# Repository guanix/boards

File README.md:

# KiCad schematic symbols and footprint libraries

I created these for my personal use, so they are not very organized.

These are no longer maintained.

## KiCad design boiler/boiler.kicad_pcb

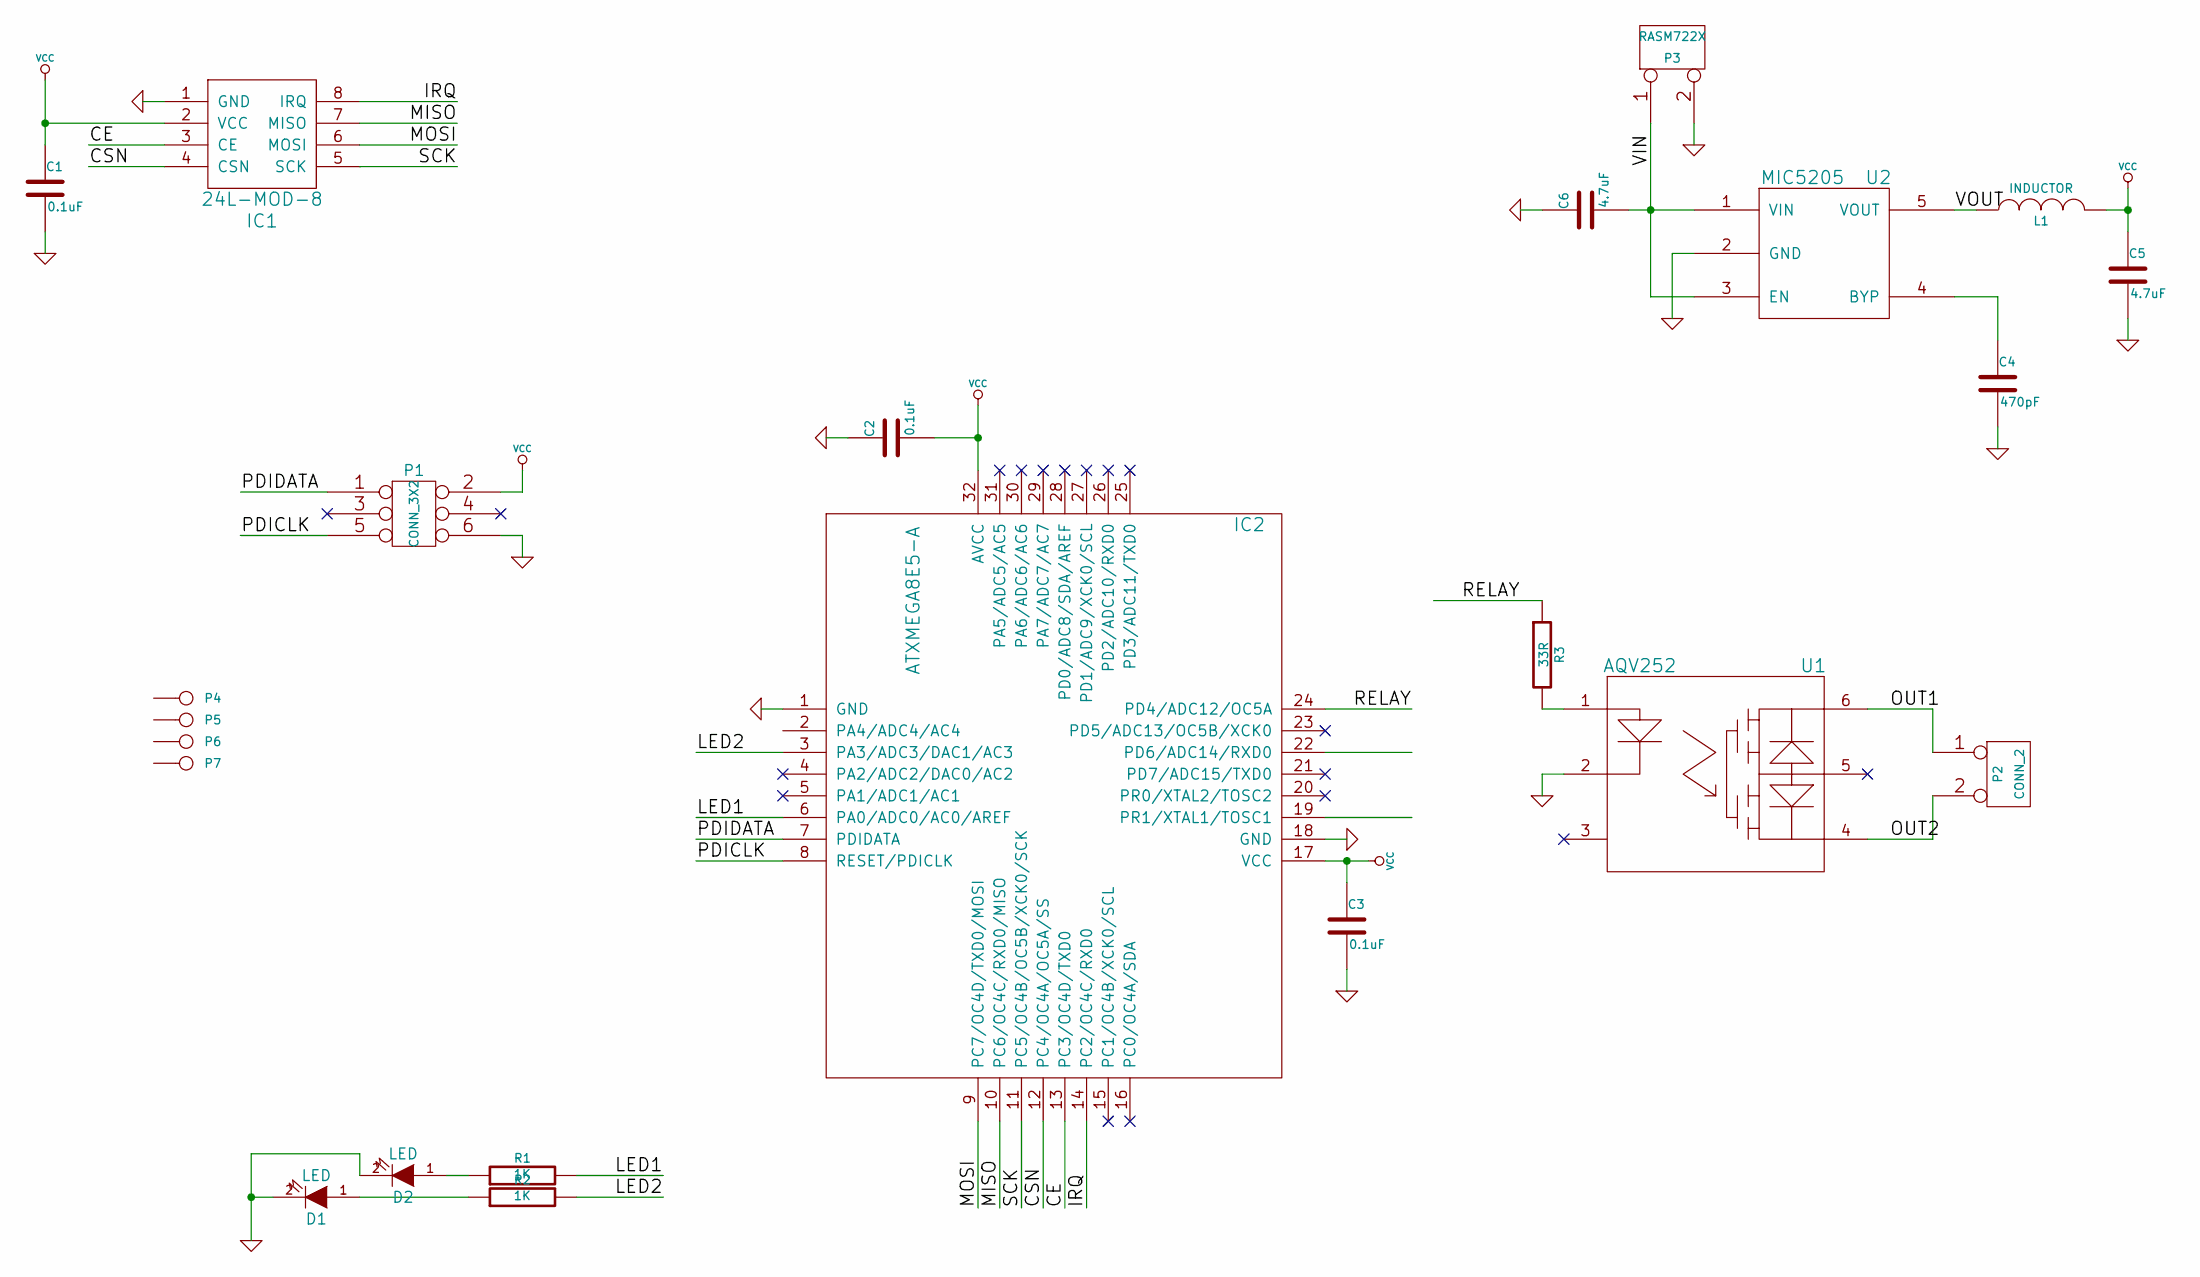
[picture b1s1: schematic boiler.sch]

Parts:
C1, C2, C3: 0.1uF
C4: 470pF
C5, C6: 4.7uF
D1, D2: LED
IC1: 24L-MOD-8
IC2: ATXMEGA8E5-A
L1: INDUCTOR
P1: CONN_3X2
P2: CONN_2
P3: RASM722X
P4, P5, P6, P7: CONN_1
R1, R2: 1K
R3: 33R
U1: AQV252
U2: MIC5205

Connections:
/CE: IC1.3 (CE), IC2.13 (PC3/OC4D/TXD0)
/CSN: IC1.4 (CSN), IC2.12 (PC4/OC4A/OC5A/SS)
/IRQ: IC1.8 (IRQ), IC2.14 (PC2/OC4C/RXD0)
/LED1: IC2.6 (PA0/ADC0/AC0/AREF), R1.2
/LED2: IC2.3 (PA3/ADC3/DAC1/AC3), R2.2
/MISO: IC1.7 (MISO), IC2.10 (PC6/OC4C/RXD0/MISO)
/MOSI: IC1.6 (MOSI), IC2.9 (PC7/OC4D/TXD0/MOSI)
/OUT1: P2.1, U1.6
/OUT2: P2.2 (PM), U1.4
/PDICLK: IC2.8 (RESET/PDICLK), P1.5
/PDIDATA: IC2.7 (PDIDATA), P1.1
/RELAY: IC2.24 (PD4/ADC12/OC5A), R3.1
/SCK: IC1.5 (SCK), IC2.11 (PC5/OC4B/OC5B/XCK0/SCK)
/VIN: C6.2, P3.1, U2.1 (VIN), U2.3 (EN)
/VOUT: L1.1, U2.5 (VOUT)
GND: C1.2, C2.1, C3.2, C4.2, C5.2, C6.1, D1.2 (K), D2.2 (K), IC1.1 (GND), IC2.1 (GND), IC2.18 (GND), P1.6, P3.2 (PM), U1.2, U2.2 (GND)
unnamed: C4.1, U2.4 (BYP)
unnamed: R3.2, U1.1
unnamed: D1.1 (A), R2.1
unnamed: D2.1 (A), R1.1
VCC: C1.1, C2.2, C3.1, C5.1, IC1.2 (VCC), IC2.17 (VCC), IC2.32 (AVCC), L1.2, P1.2

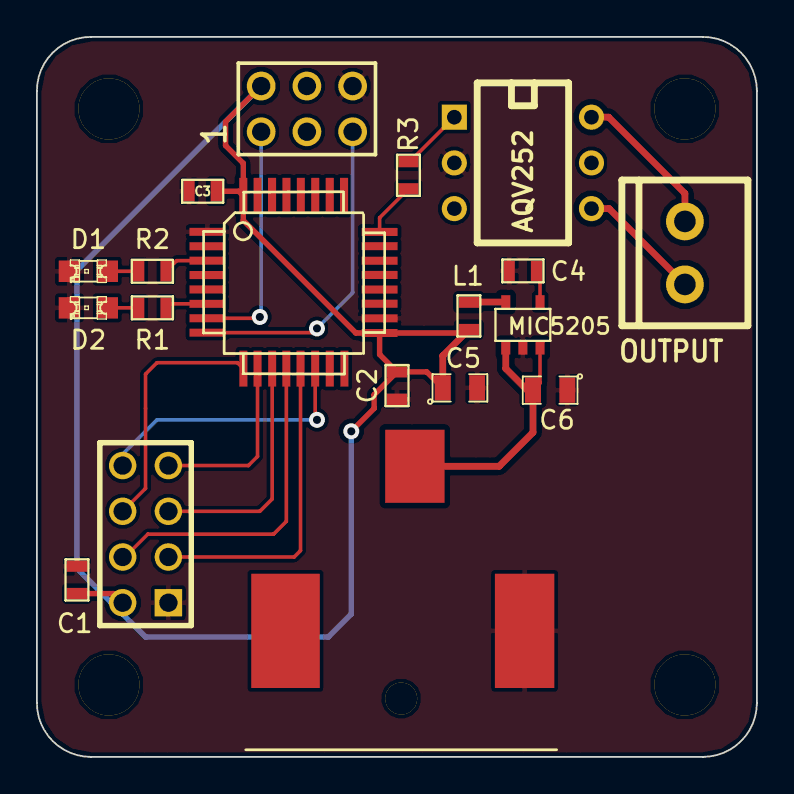
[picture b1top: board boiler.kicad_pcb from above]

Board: 2 copper layers, 40.0 x 40.0 mm, 23 parts (0 on the bottom side), 21 nets.

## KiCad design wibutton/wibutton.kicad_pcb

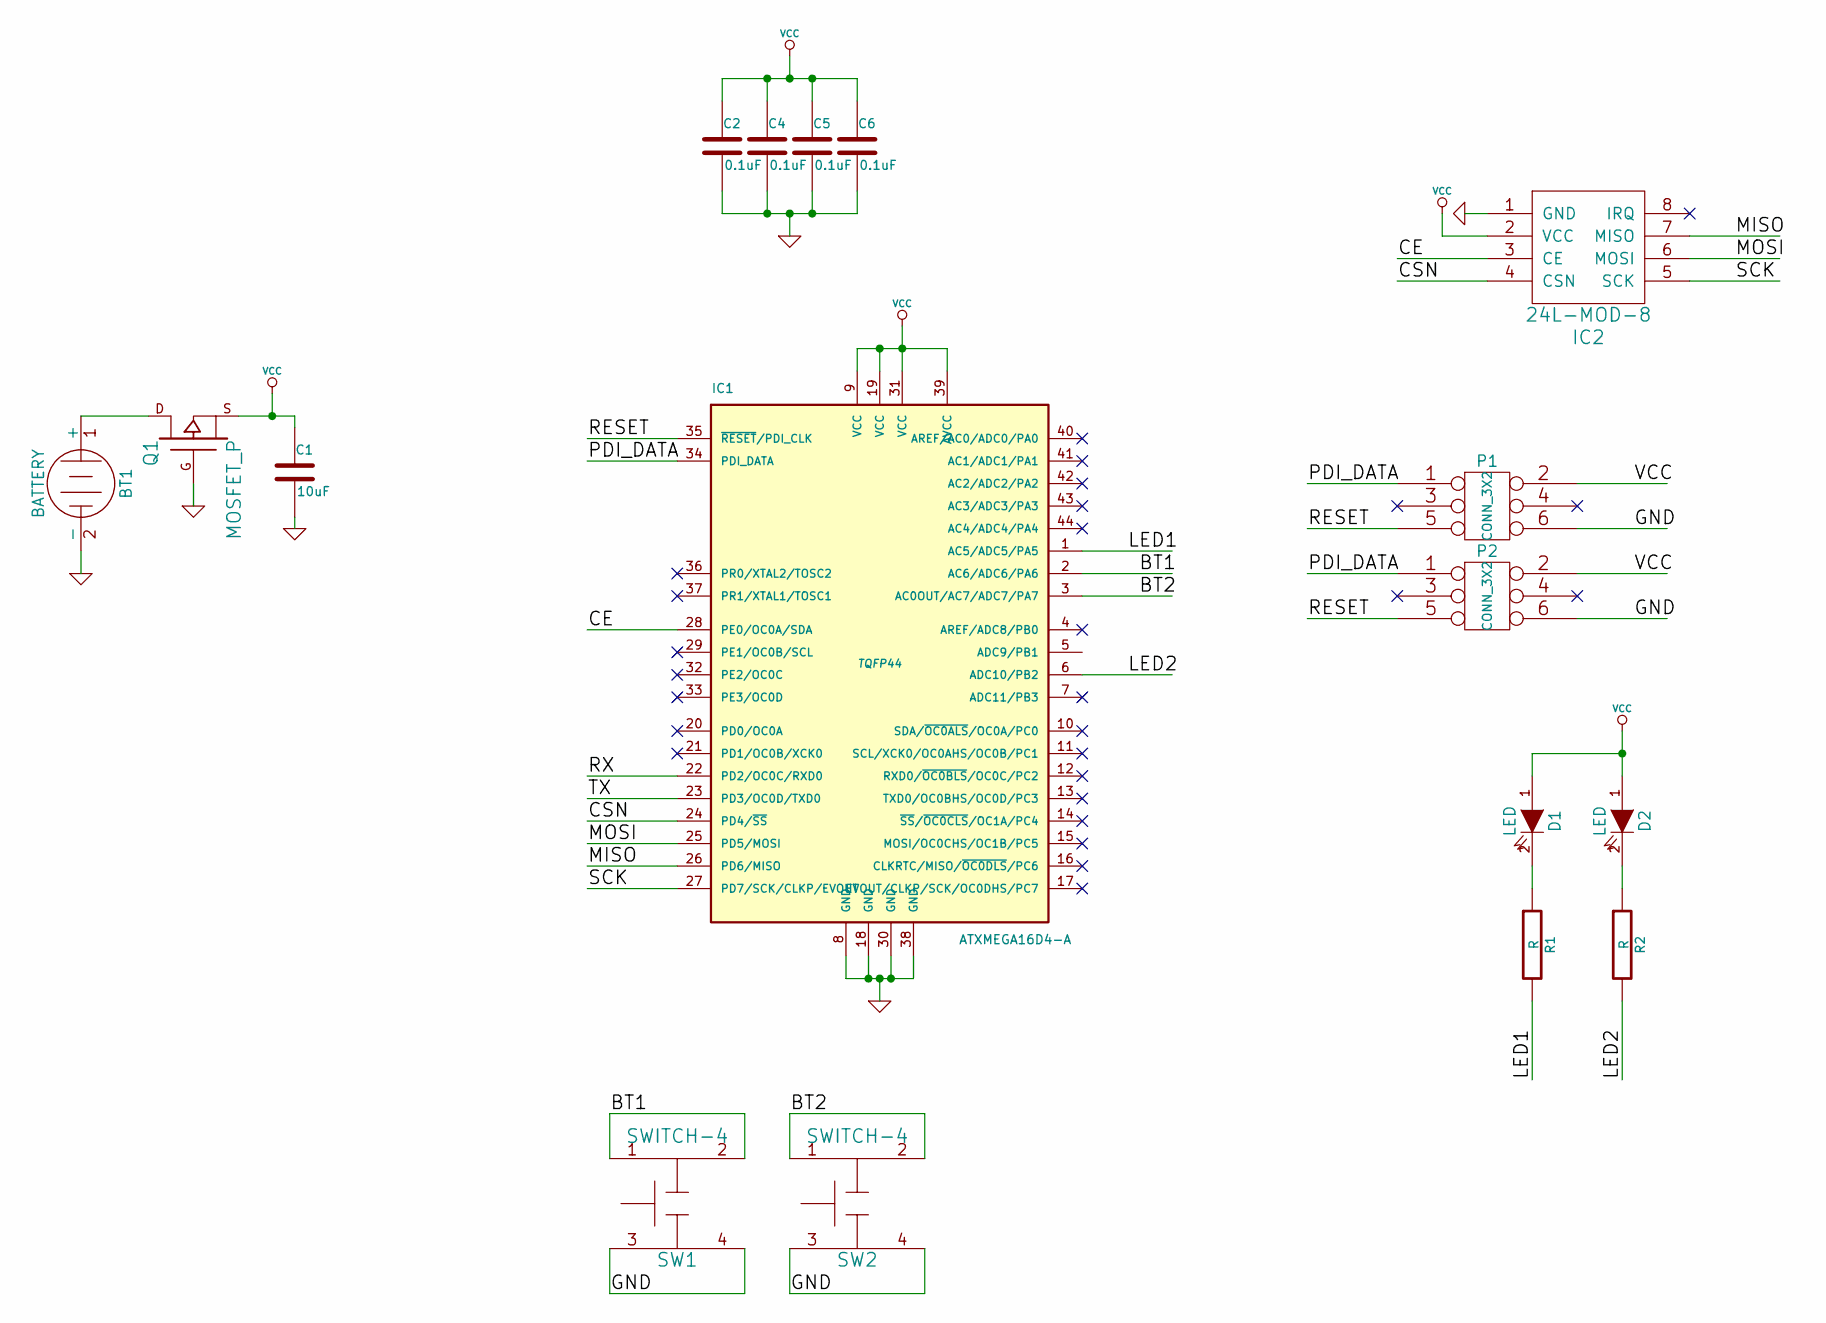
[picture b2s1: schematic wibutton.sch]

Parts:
BT1: BATTERY
C1: 10uF
C2, C4, C5, C6: 0.1uF
D1, D2: LED
IC1: ATXMEGA16D4-A; TQFP44
IC2: 24L-MOD-8
P1, P2: CONN_3X2
Q1: MOSFET_P
R1, R2: R
SW1, SW2: SWITCH-4

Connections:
/BT1: IC1.2 (AC6/ADC6/PA6), SW1.1, SW1.2
/BT2: IC1.3 (AC0OUT/AC7/ADC7/PA7), SW2.1, SW2.2
/CE: IC1.28 (PE0/OC0A/SDA), IC2.3 (CE)
/CSN: IC1.24 (PD4/~SS~), IC2.4 (CSN)
/LED1: IC1.1 (AC5/ADC5/PA5), R1.2
/LED2: IC1.6 (ADC10/PB2), R2.2
/MISO: IC1.26 (PD6/MISO), IC2.7 (MISO)
/MOSI: IC1.25 (PD5/MOSI), IC2.6 (MOSI)
/PDI_DATA: IC1.34 (PDI_DATA), P1.1, P2.1
/RESET: IC1.35 (~RESET~/PDI_CLK), P1.5, P2.5
/RX: IC1.22 (PD2/OC0C/RXD0)
/SCK: IC1.27 (PD7/SCK/CLKP/EVOUT), IC2.5 (SCK)
/TX: IC1.23 (PD3/OC0D/TXD0)
GND: BT1.2 (-), C1.2, C2.2, C4.2, C5.2, C6.2, IC1.8 (GND), IC1.18 (GND), IC1.30 (GND), IC1.38 (GND), IC2.1 (GND), P1.6, P2.6, Q1.G, SW1.3, SW1.4, SW2.3, SW2.4
unnamed: D1.2 (K), R1.1
unnamed: D2.2 (K), R2.1
unnamed: BT1.1 (+), Q1.D
VCC: C1.1, C2.1, C4.1, C5.1, C6.1, D1.1 (A), D2.1 (A), IC1.9 (VCC), IC1.19 (VCC), IC1.31 (VCC), IC1.39 (AVCC), IC2.2 (VCC), P1.2, P2.2, Q1.S

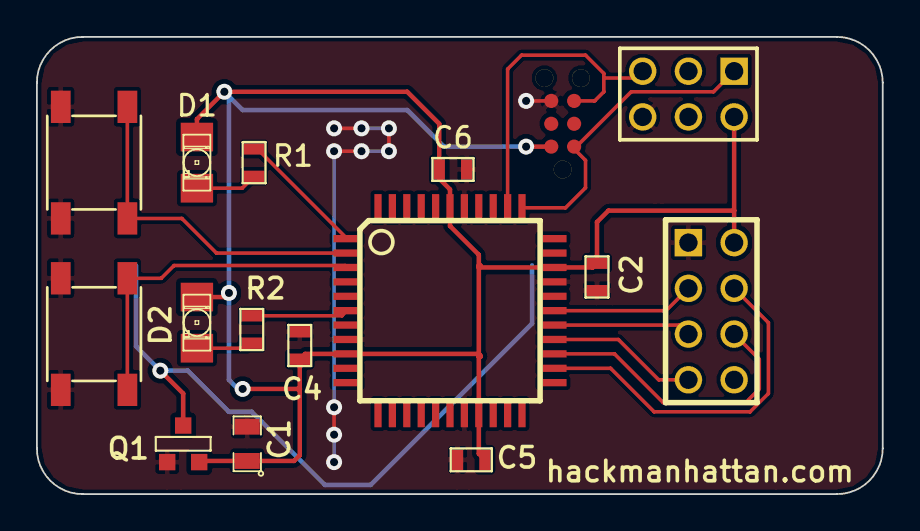
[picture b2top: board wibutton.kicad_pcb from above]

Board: 2 copper layers, 47.0 x 25.4 mm, 17 parts (1 on the bottom side), 16 nets.

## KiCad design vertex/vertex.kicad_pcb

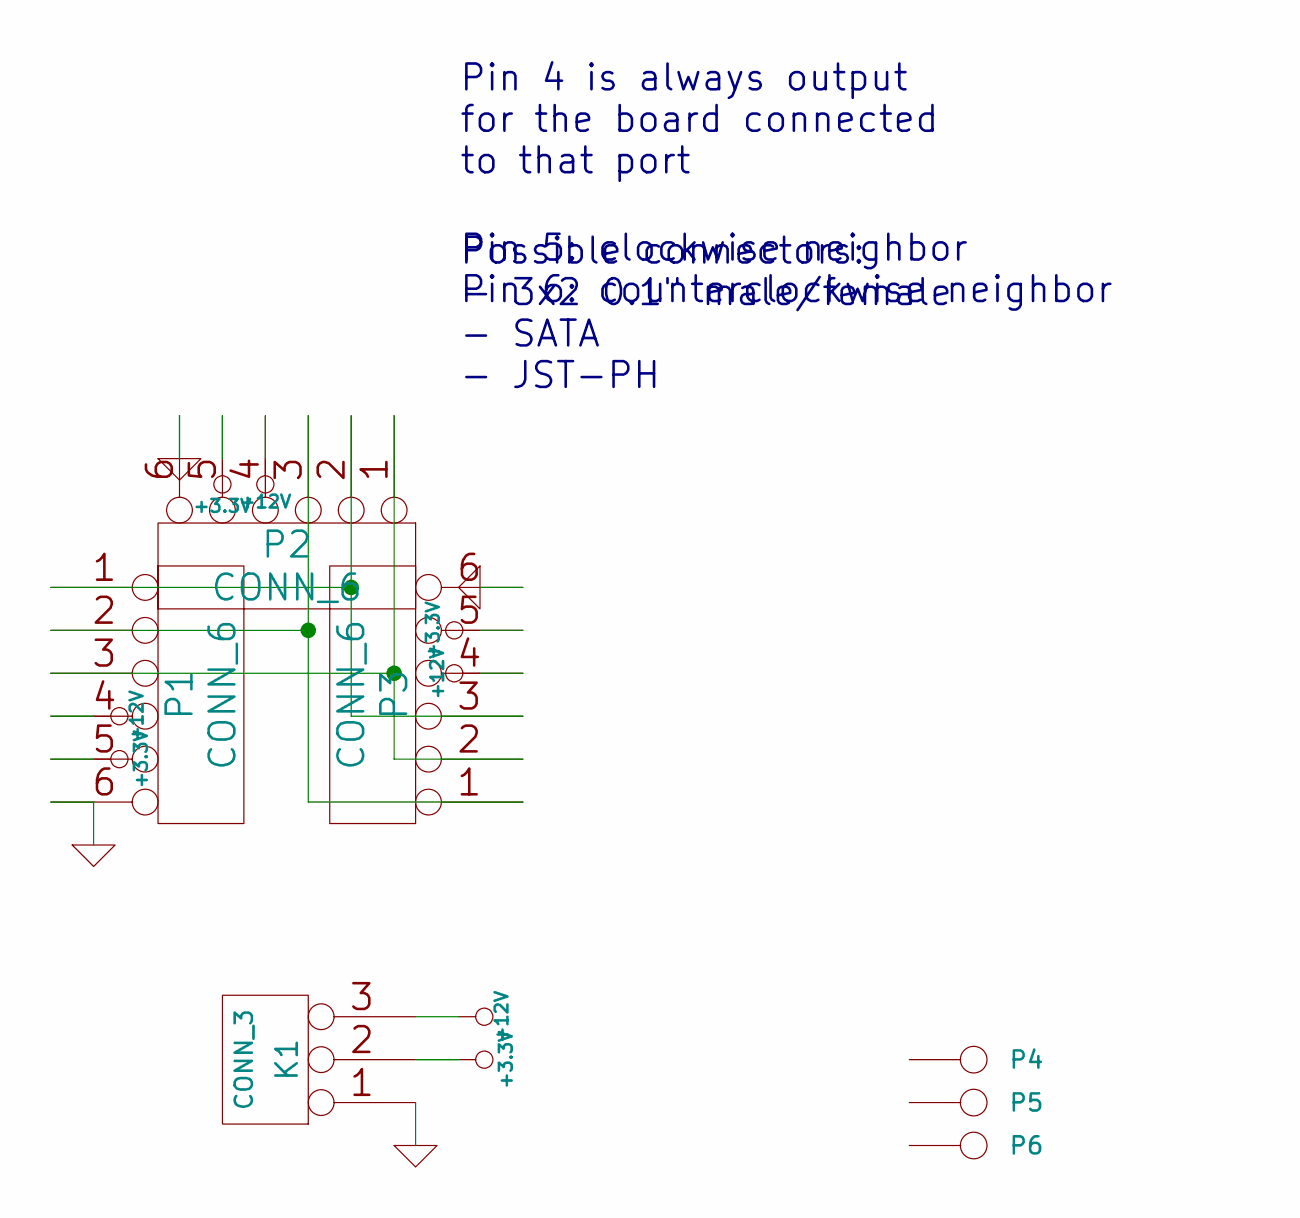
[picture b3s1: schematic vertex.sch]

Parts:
K1: CONN_3
P1, P2, P3: CONN_6
P4, P5, P6: CONN_1

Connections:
+3.3V: K1.2 (PM), P1.5, P2.5, P3.5
+12V: K1.3, P1.4, P2.4, P3.4
GND: K1.1, P1.6, P2.6, P3.6
unnamed: P1.2, P2.3, P3.1
unnamed: P1.3, P2.1, P3.2
unnamed: P1.1, P2.2, P3.3

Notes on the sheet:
Pin 4 is always output for the board connected to that port
Possible connectors: - 3x2 0.1" male/female - SATA - JST-PH
Pin 5: clockwise neighbor Pin 6: counterclockwise neighbor

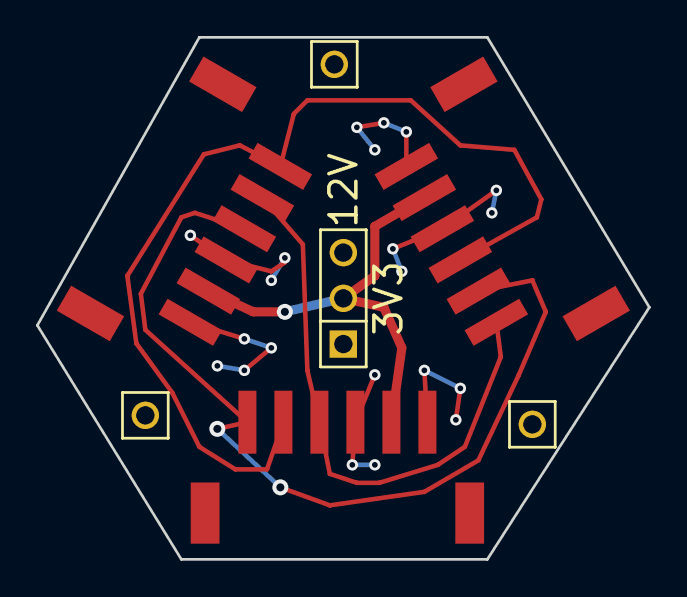
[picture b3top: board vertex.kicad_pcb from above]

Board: 2 copper layers, 34.0 x 29.0 mm, 7 parts (0 on the bottom side), 6 nets.

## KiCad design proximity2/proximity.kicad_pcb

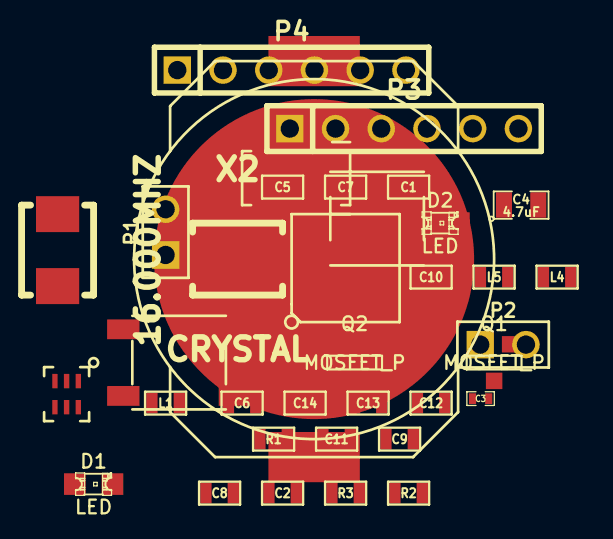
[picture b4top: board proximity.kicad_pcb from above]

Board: 2 copper layers, 36 parts (0 on the bottom side), 34 nets, no tracks yet.

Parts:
B1: BALUN-JOHANSON
BT1: BATTERY; BAT-BK912
C1, C2, C8, C11: 0.1uF; SM0603
C3: 2.2nF; SM0402
C4: 4.7uF; SM0805
C5, C6, C13, C14: 12pF; SM0603
C7: 4.7uF; SM0603
C9: 1nF; SM0603
C10: 47nF; SM0603
C12: 1uF; SM0603
D1, D2: LED; LED-0805
IC1: NRF51822; QFN48+1-0.4MM-SHORTPADS
L1: INDUCTOR; SM0603
L4: 10uH; SM0603
L5: 15nH; SM0603
P1, P2: CONN_2; PIN_ARRAY_2X1
P3: AIN_0_3; PIN_ARRAY-6X1
P4: AIN_4_7; PIN_ARRAY-6X1
Q1, Q2: MOSFET_P; SOT23GDS
R1: 12K; SM0603
R2, R3: 100R; SM0603
SW1, SW2: SWITCH-4; SWITCH-ALPS
U1: ANTENNA-NC; ANTENNA-JOHANSON-2.45GHZ
X1: 16.000MHZ; CRYSTAL-NX5032GA
X2: CRYSTAL; CRYSTAL-NX5032GA

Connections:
/AIN2: IC1.5, P3.5
/AIN3: IC1.6, P3.6
/AIN4: IC1.7, P4.3
/AIN5: IC1.8, P4.4
/AIN6: IC1.9, P4.5
/AIN7: IC1.10, P4.6
/ANT1: B1.4, IC1.31
/ANT2: B1.3, IC1.32
/LED1: IC1.15, R2.2
/LED2: IC1.16, R3.2
/P7: IC1.11, P3.3
/P8: IC1.14, P3.4
/SW1: IC1.48, SW1.3, SW1.4
/SW2: IC1.47, SW2.3, SW2.4
/SWCLK: IC1.24, P1.2, R1.1
/SWDIO: IC1.23, P1.1
/VDD_PA: B1.5, C3.1, IC1.30
AVDD: C9.1, C12.1, IC1.35, IC1.36, L5.1
GND: B1.2, BT1.2, C2.1, C3.2, C4.2, C5.1, C6.1, C7.2, C8.2, C9.2, C10.2, C11.2, C12.2, C13.1, C14.1, IC1.13, IC1.33, IC1.34, IC1.49, P2.2, P3.1, P4.1, Q1.G, Q2.G, R1.2, SW1.1, SW1.2, SW2.1, SW2.2
unnamed: C10.1, IC1.29
unnamed: D2.2, R3.1
unnamed: D1.2, R2.1
unnamed: B1.1, U1.1
unnamed: L4.1, L5.2
unnamed: C5.2, IC1.38, X1.2
unnamed: C6.2, IC1.37, X1.1
unnamed: C8.1, IC1.39
unnamed: IC1.2, L4.2
unnamed: C14.2, IC1.45, X2.2
unnamed: C13.2, IC1.46, X2.1
unnamed: P2.1, Q1.D
unnamed: L1.1, Q1.S, Q2.S
unnamed: BT1.1, Q2.D
VCC: C1.2, C2.2, C4.1, C7.1, C11.1, D1.1, D2.1, IC1.1, IC1.12, L1.2, P3.2, P4.2

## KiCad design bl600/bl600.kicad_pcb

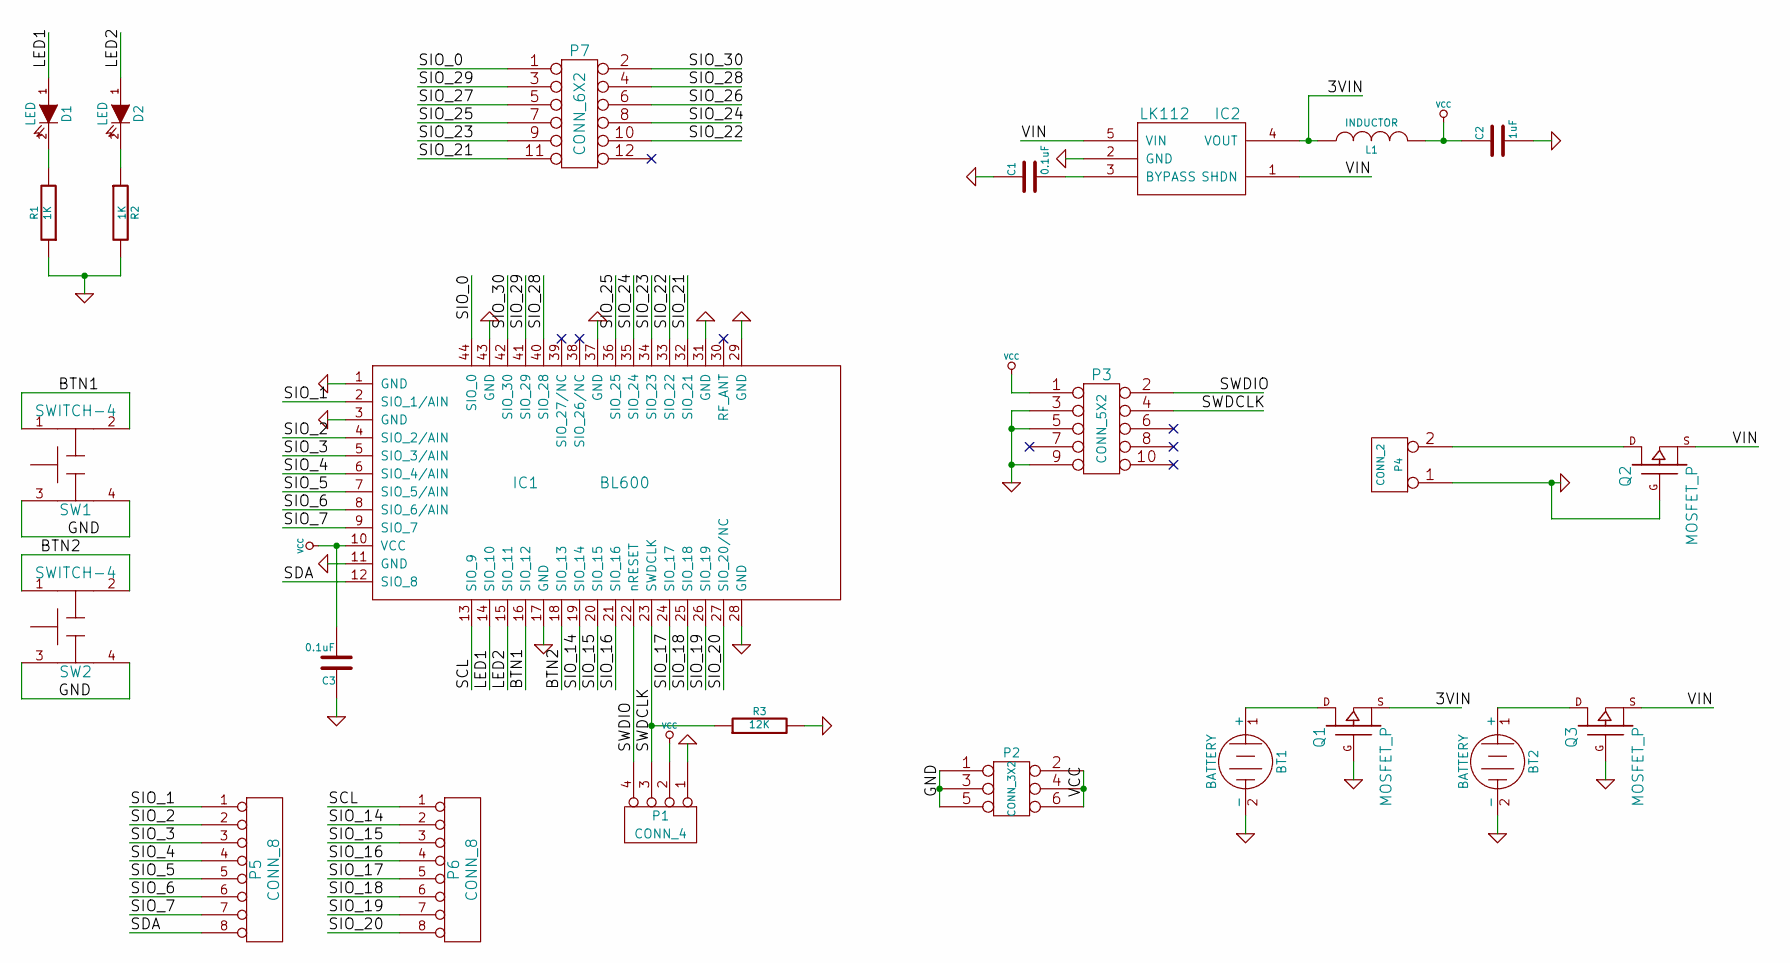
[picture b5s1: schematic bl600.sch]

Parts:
BT1, BT2: BATTERY
C1, C3: 0.1uF
C2: 1uF
D1, D2: LED
IC1: BL600
IC2: LK112
L1: INDUCTOR
P1: CONN_4
P2: CONN_3X2
P3: CONN_5X2
P4: CONN_2
P5, P6: CONN_8
P7: CONN_6X2
Q1, Q2, Q3: MOSFET_P
R1, R2: 1K
R3: 12K
SW1, SW2: SWITCH-4

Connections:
/3VIN: IC2.4 (VOUT), L1.1, Q1.S
/BTN1: IC1.16 (SIO_12), SW1.1, SW1.2
/BTN2: IC1.18 (SIO_13), SW2.1, SW2.2
/LED1: D1.1 (A), IC1.14 (SIO_10)
/LED2: D2.1 (A), IC1.15 (SIO_11)
/SCL: IC1.13 (SIO_9), P6.1
/SDA: IC1.12 (SIO_8), P5.8
/SIO_0: IC1.44 (SIO_0), P7.1
/SIO_1: IC1.2 (SIO_1/AIN), P5.1
/SIO_2: IC1.4 (SIO_2/AIN), P5.2
/SIO_3: IC1.5 (SIO_3/AIN), P5.3
/SIO_4: IC1.6 (SIO_4/AIN), P5.4
/SIO_5: IC1.7 (SIO_5/AIN), P5.5
/SIO_6: IC1.8 (SIO_6/AIN), P5.6
/SIO_7: IC1.9 (SIO_7), P5.7
/SIO_14: IC1.19 (SIO_14), P6.2
/SIO_15: IC1.20 (SIO_15), P6.3
/SIO_16: IC1.21 (SIO_16), P6.4
/SIO_17: IC1.24 (SIO_17), P6.5
/SIO_18: IC1.25 (SIO_18), P6.6
/SIO_19: IC1.26 (SIO_19), P6.7
/SIO_20: IC1.27 (SIO_20/NC), P6.8
/SIO_21: IC1.32 (SIO_21), P7.11
/SIO_22: IC1.33 (SIO_22), P7.10
/SIO_23: IC1.34 (SIO_23), P7.9
/SIO_24: IC1.35 (SIO_24), P7.8
/SIO_25: IC1.36 (SIO_25), P7.7
/SIO_26: P7.6
/SIO_27: P7.5
/SIO_28: IC1.40 (SIO_28), P7.4
/SIO_29: IC1.41 (SIO_29), P7.3
/SIO_30: IC1.42 (SIO_30), P7.2
/SWDCLK: IC1.23 (SWDCLK), P1.3, P3.4, R3.1
/SWDIO: IC1.22 (nRESET), P1.4, P3.2
/VIN: IC2.1 (SHDN), IC2.5 (VIN), Q2.S, Q3.S
GND: BT1.2 (-), BT2.2 (-), C1.1, C2.2, C3.1, IC1.1 (GND), IC1.3 (GND), IC1.11 (GND), IC1.17 (GND), IC1.28 (GND), IC1.29 (GND), IC1.31 (GND), IC1.37 (GND), IC1.43 (GND), IC2.2 (GND), P1.1, P2.1, P2.3, P2.5, P3.3, P3.5, P3.9, P4.1, Q1.G, Q2.G, Q3.G, R1.1, R2.2, R3.2, SW1.3, SW1.4, SW2.3, SW2.4
unnamed: D2.2 (K), R2.1
unnamed: D1.2 (K), R1.2
unnamed: BT1.1 (+), Q1.D
unnamed: P4.2 (PM), Q2.D
unnamed: BT2.1 (+), Q3.D
unnamed: C1.2, IC2.3 (BYPASS)
VCC: C2.1, C3.2, IC1.10 (VCC), L1.2, P1.2, P2.2, P2.4, P2.6, P3.1

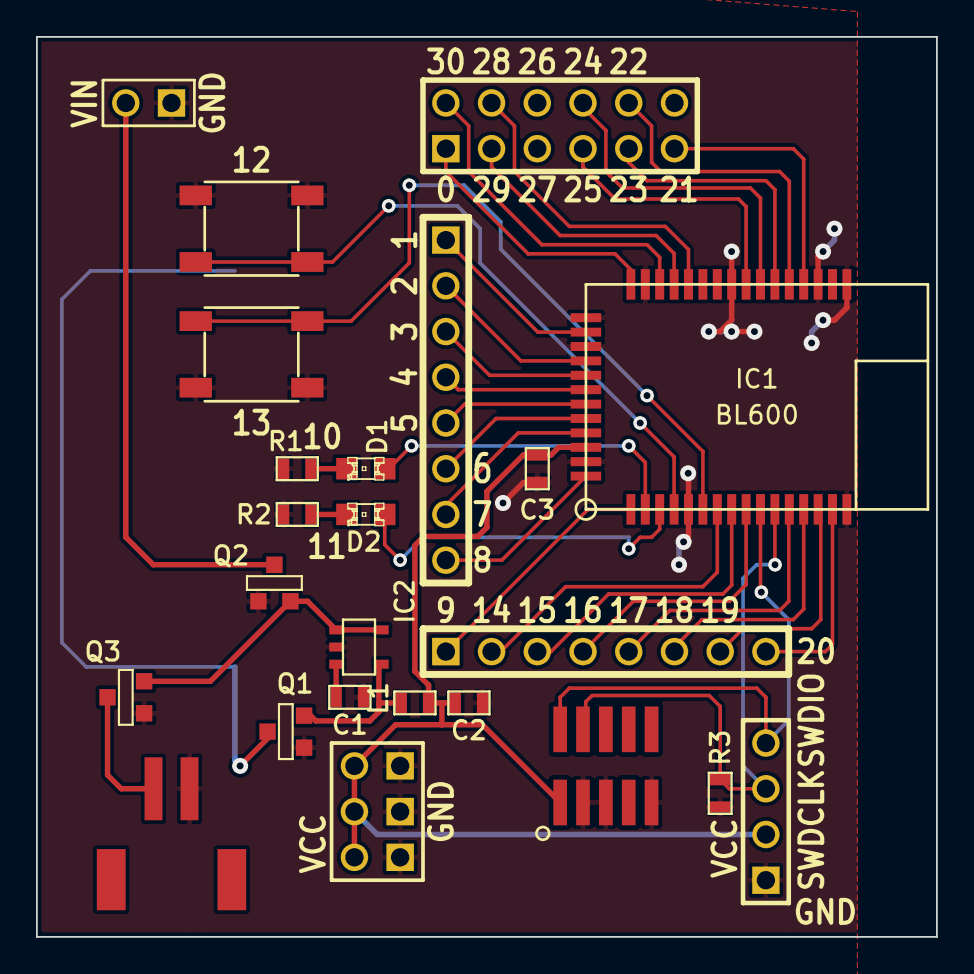
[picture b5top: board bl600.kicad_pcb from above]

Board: 2 copper layers, 50.0 x 50.0 mm, 25 parts (1 on the bottom side), 41 nets.

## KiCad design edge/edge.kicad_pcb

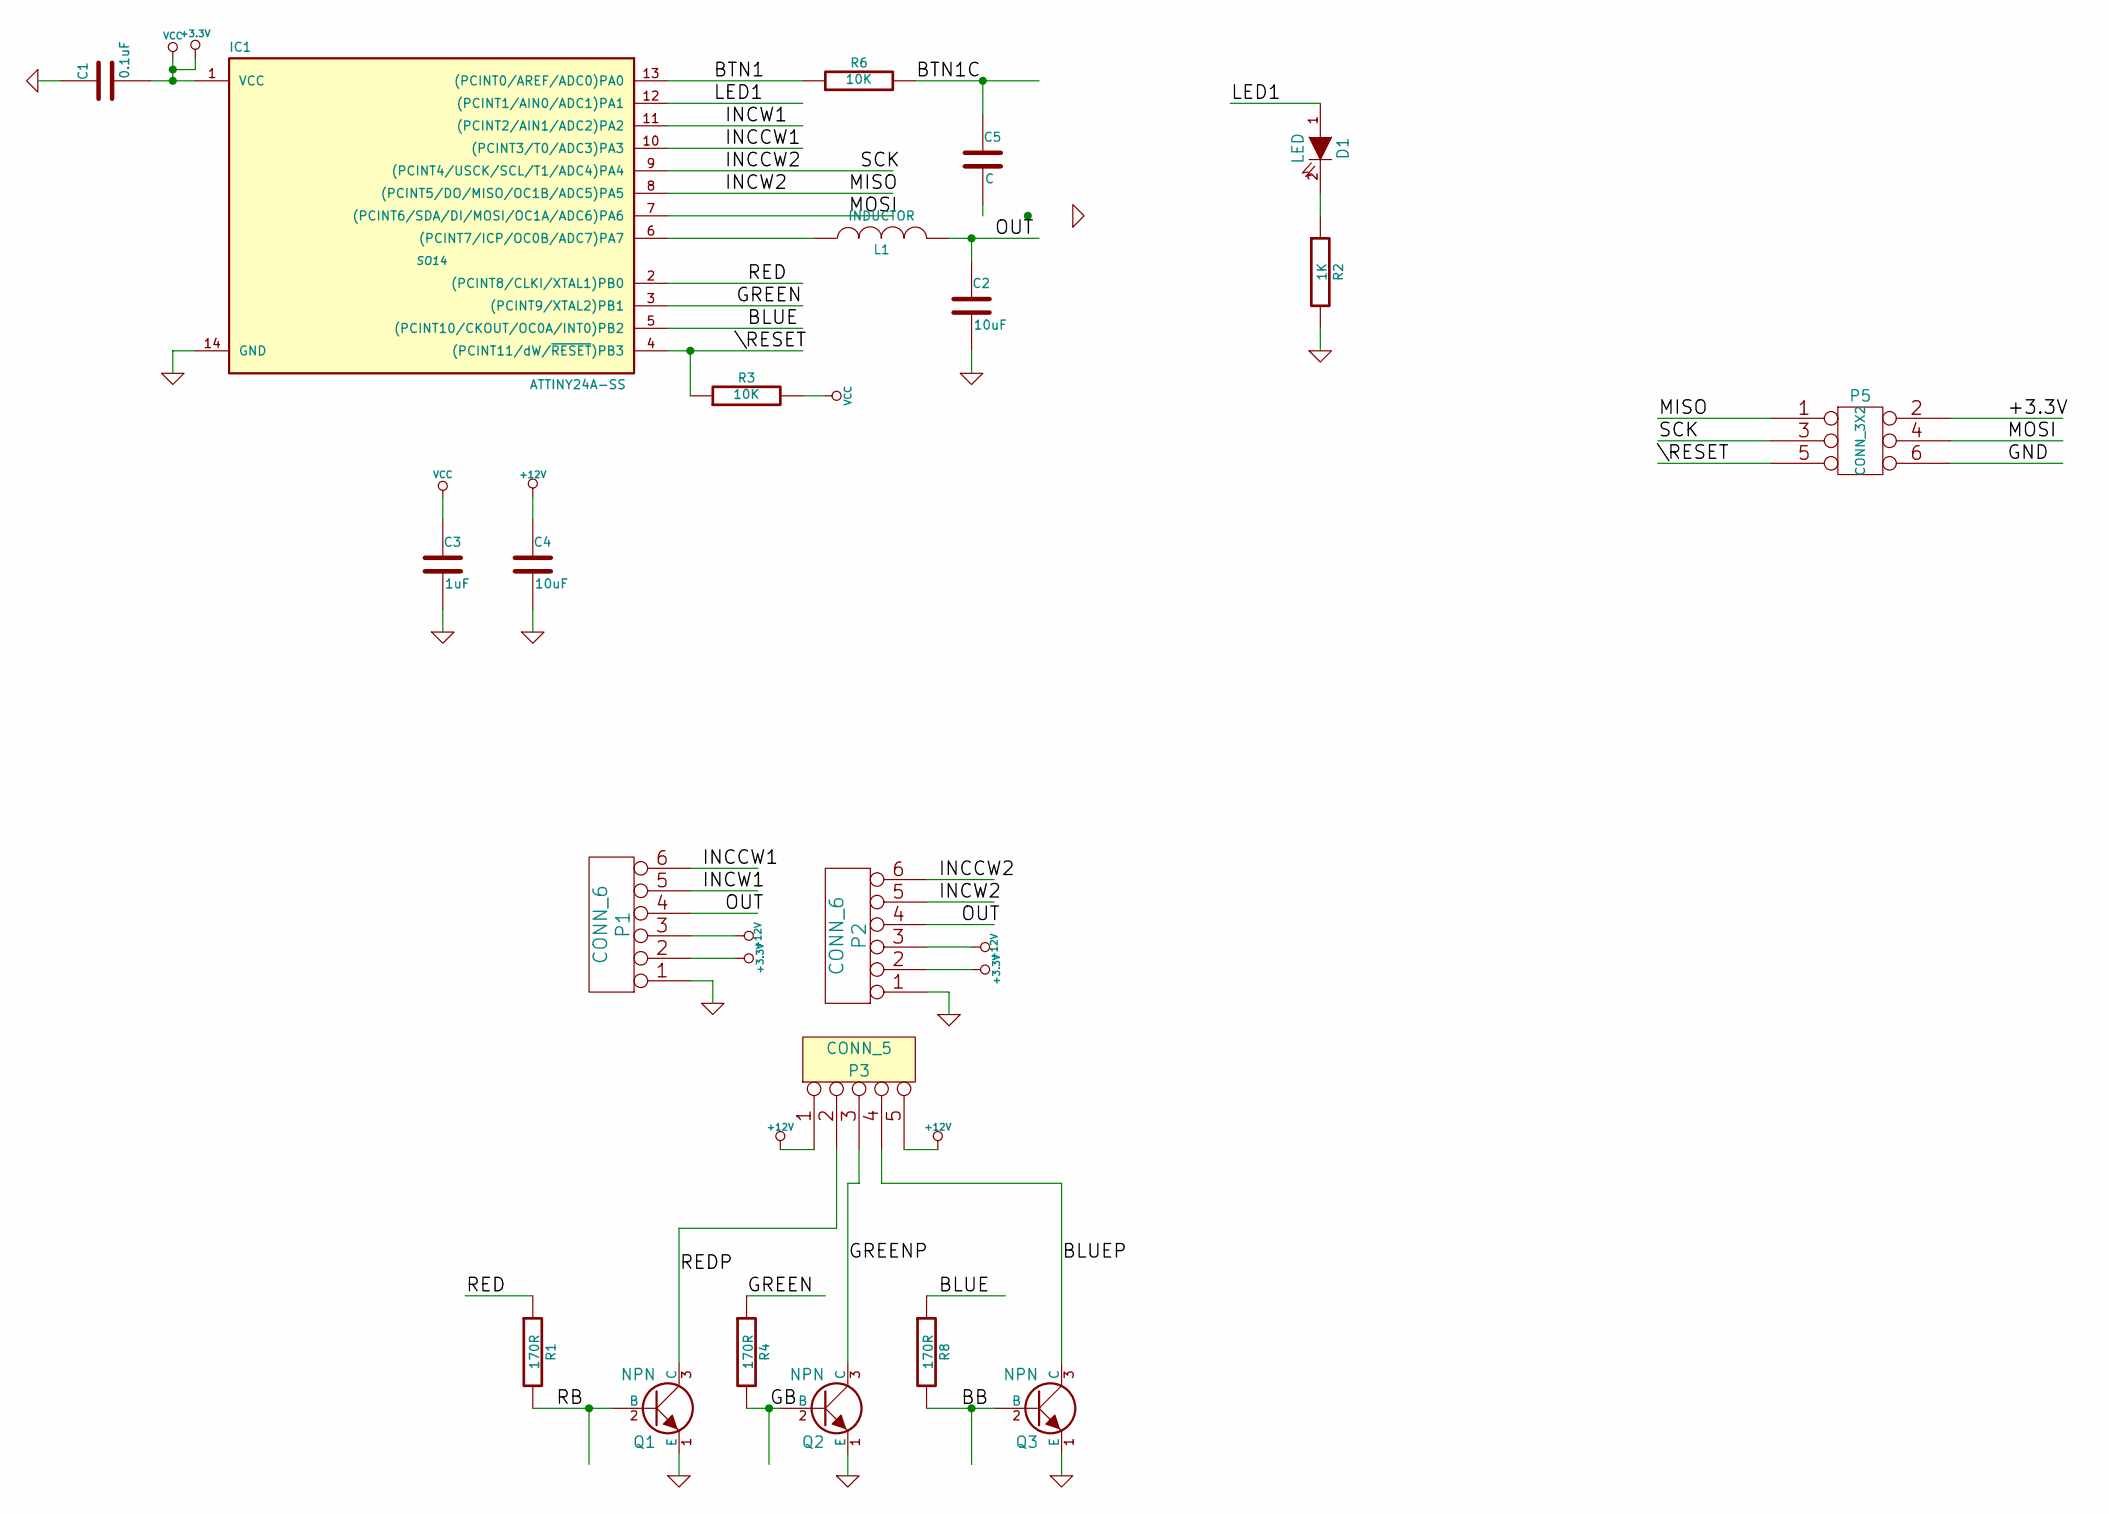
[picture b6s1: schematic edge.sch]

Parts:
C1: 0.1uF
C2, C4: 10uF
C3: 1uF
C5: C
D1: LED
IC1: ATTINY24A-SS; SO14
L1: INDUCTOR
P1, P2: CONN_6
P3: CONN_5
P5: CONN_3X2
Q1, Q2, Q3: NPN
R1, R4, R8: 170R
R2: 1K
R3, R6: 10K

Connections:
+3.3V: C1.2, C3.1, IC1.1 (VCC), P1.2, P2.2, P5.2, R3.2
+12V: C4.1, P1.3, P2.3, P3.1, P3.5
/BB: Q3.2 (B), R8.2
/BLUE: IC1.5 ((PCINT10/CKOUT/OC0A/INT0)PB2), R8.1
/BLUEP: P3.4, Q3.3 (C)
/BTN1: IC1.13 ((PCINT0/AREF/ADC0)PA0), R6.1
/BTN1C: C5.1, R6.2
/GB: Q2.2 (B), R4.2
/GREEN: IC1.3 ((PCINT9/XTAL2)PB1), R4.1
/GREENP: P3.3, Q2.3 (C)
/INCCW1: IC1.10 ((PCINT3/T0/ADC3)PA3), P1.6
/INCCW2: IC1.9 ((PCINT4/USCK/SCL/T1/ADC4)PA4), P2.6, P5.3
/INCW1: IC1.11 ((PCINT2/AIN1/ADC2)PA2), P1.5
/INCW2: IC1.8 ((PCINT5/DO/MISO/OC1B/ADC5)PA5), P2.5, P5.1
/LED1: D1.1 (A), IC1.12 ((PCINT1/AIN0/ADC1)PA1)
/MOSI: IC1.7 ((PCINT6/SDA/DI/MOSI/OC1A/ADC6)PA6), P5.4
/OUT: C2.1, L1.2, P1.4, P2.4
/RB: Q1.2 (B), R1.2
/RED: IC1.2 ((PCINT8/CLKI/XTAL1)PB0), R1.1
/REDP: P3.2, Q1.3 (C)
/\RESET: IC1.4 ((PCINT11/dW/~RESET~)PB3), P5.5, R3.1
GND: C1.1, C2.2, C3.2, C4.2, IC1.14 (GND), P1.1, P2.1, P5.6, Q1.1 (E), Q2.1 (E), Q3.1 (E), R2.2
unnamed: D1.2 (K), R2.1
unnamed: IC1.6 ((PCINT7/ICP/OC0B/ADC7)PA7), L1.1

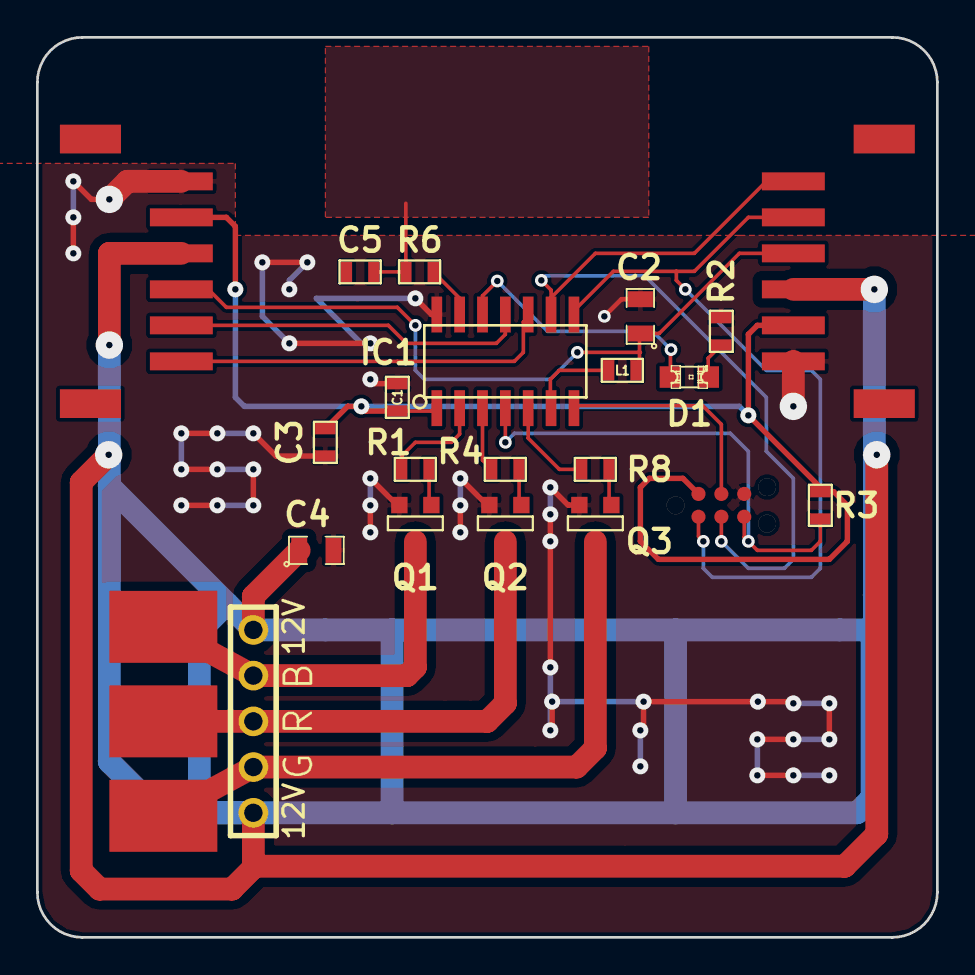
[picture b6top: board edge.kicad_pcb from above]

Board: 2 copper layers, 50.0 x 50.0 mm, 21 parts (0 on the bottom side), 24 nets.

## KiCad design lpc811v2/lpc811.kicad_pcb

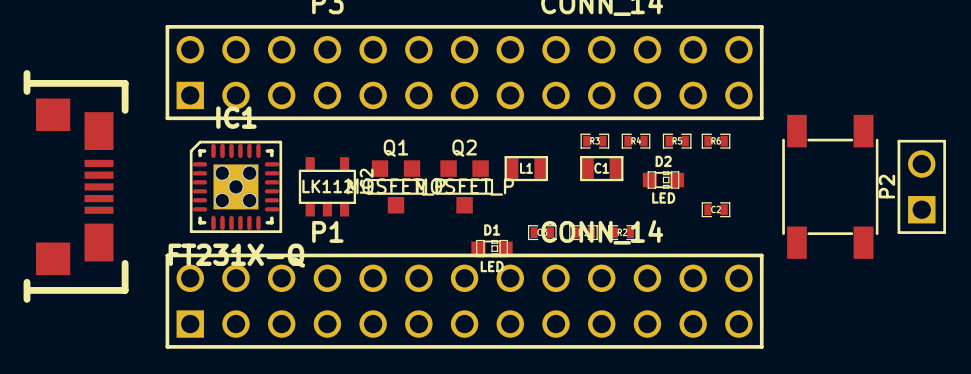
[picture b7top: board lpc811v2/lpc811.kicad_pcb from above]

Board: 2 copper layers, 21 parts (0 on the bottom side), 14 nets, no tracks yet.

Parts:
C1: 1uF; SM0603
C2: 0.1uF; SM0402_c
C3: 1uF; SM0402_c
D1, D2: LED; LED-0603
IC1: FT231X-Q; QFN24
IC2: LK112; SOT23-5
J1: MINI-USB-SHLD; MICROUSB-B-ZX62-B-5PA
L1: INDUCTOR; SM0603
P1, P3: CONN_14; pin_array_13x2
P2: CONN_2; PIN_ARRAY_2X1
Q1, Q2: MOSFET_P; SOT23GDS
R1, R2: 10K; SM0402_r
R3, R4: 27R; SM0402_r
R5, R6: 470R; SM0402_r
SW1: SWITCH-4; SWITCH-ALPS

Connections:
/D+: IC1.8, IC1.9, IC1.10, IC1.11, IC1.20, R3.2, R4.2
/PIO0_12: P1.12, SW1.1, SW1.2
/PIO0_13: D2.1, P1.13
/VIN: P3.14, Q2.D
/VREGIN: C1.1, IC2.1, IC2.5, Q1.S, Q2.S
/VUSB: IC1.12, J1.1, Q1.D
GND: C1.2, C2.2, C3.1, IC1.3, IC1.13, IC1.21, IC2.2, J1.5, P2.1, P3.9, P3.10, P3.11, R1.1, R2.2, R5.2, R6.2, SW1.3, SW1.4
unnamed: D1.2, R5.1
unnamed: Q2.G, R2.1
unnamed: Q1.G, R1.2
unnamed: IC2.4, L1.1
unnamed: D2.2, R6.1
unnamed: C2.1, IC2.3
VCC: C3.2, D1.1, L1.2, P2.2, P3.12, P3.13
